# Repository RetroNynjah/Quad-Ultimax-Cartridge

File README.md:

# Retro Ninja Quad Ultimax Cartridge

Eagle schematics and board for a C64 Ultimax cartridge with two-bit ROM selector DIP switch (or jumpers). It's based on a 27256 type EPROM and can fit four 64Kbit (8KB) Ultimax ROM images.

Combine up to four 8KB ROM files into one bigger file before burning EPROM.

The DIP switch is optional. Leave it out if all you need is one 8KB ROM. The DIP switch can also be replaced by a couple of jumpers.

Gerber files and 3D-printable enclosure included.

## BOM
 |Component|Pcs |Name|Comment|
 |:--------|---:|:---|:------|
 | 27256/27C256 EPROM DIP-28| 1 | IC1 | Or compatible EPROM |
 | 2-pos dip switch | 1 | BT1| Optional. CT2062-ND from Digikey or similar | 
 | 100nF ceramic capacitor | 1 | C1 ||
 | 10k resistor | 2 | R1, R2 ||
 
Retro Ninja

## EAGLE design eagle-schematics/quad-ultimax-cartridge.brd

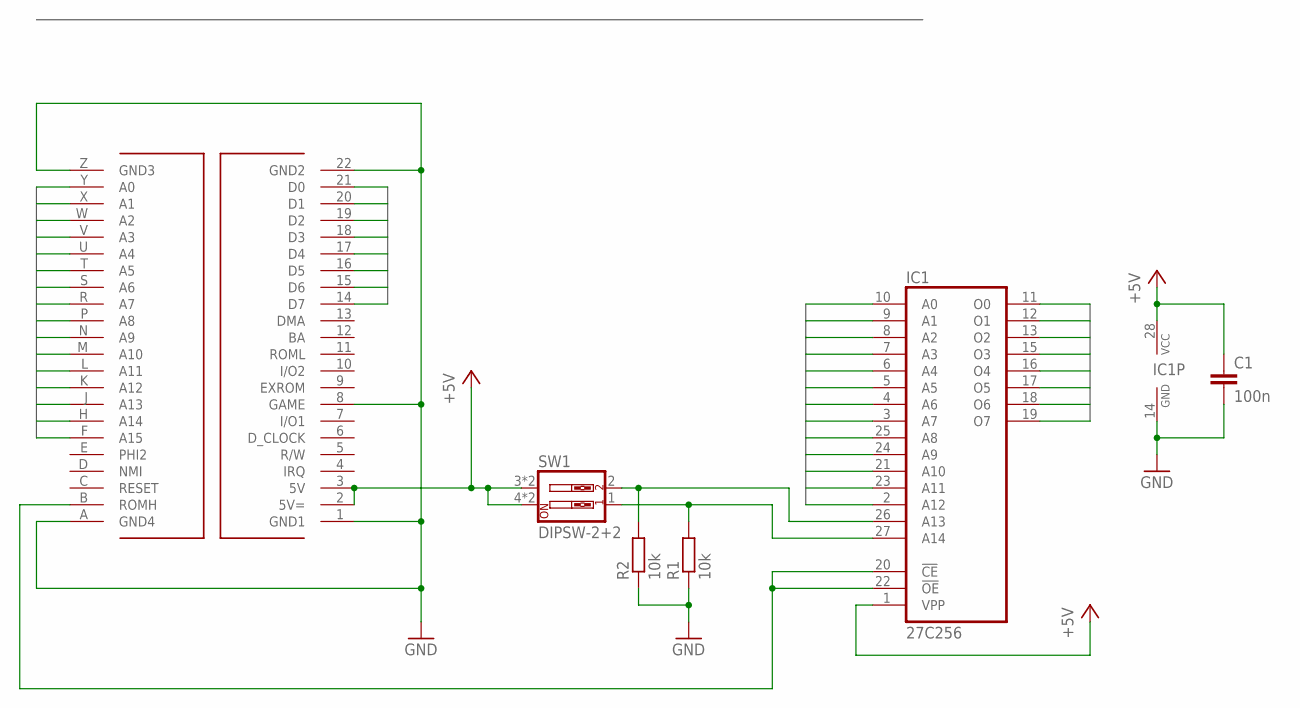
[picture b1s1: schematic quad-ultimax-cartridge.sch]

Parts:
C1: 100n; CAP_5MM_2.5X5.0_ROUND
IC1: 27C256; DIL28
R1, R2: 10k; 0207/10
SW1: DIPSW-2+2; DIPSW2+2
U$1: C64CARTRIDGE_BOARD_CONNECTOR; C64_CARTRIDGE_BOARDEDGE

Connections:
+5V: C1.1, IC1.1 (VPP), IC1.28 (VCC), SW1.3, SW1.4, SW1.5 (3), SW1.6 (4), U$1.2 (5V=), U$1.3 (5V)
A0: IC1.10 (A0), U$1.Y (A0)
A1: IC1.9 (A1), U$1.X (A1)
A2: IC1.8 (A2), U$1.W (A2)
A3: IC1.7 (A3), U$1.V (A3)
A4: IC1.6 (A4), U$1.U (A4)
A5: IC1.5 (A5), U$1.T (A5)
A6: IC1.4 (A6), U$1.S (A6)
A7: IC1.3 (A7), U$1.R (A7)
A8: IC1.25 (A8), U$1.P (A8)
A9: IC1.24 (A9), U$1.N (A9)
A10: IC1.21 (A10), U$1.M (A10)
A11: IC1.23 (A11), U$1.L (A11)
A12: IC1.2 (A12), U$1.K (A12)
A13: U$1.J (A13)
A14: U$1.H (A14)
A15: U$1.F (A15)
D0: IC1.11 (O0), U$1.21 (D0)
D1: IC1.12 (O1), U$1.20 (D1)
D2: IC1.13 (O2), U$1.19 (D2)
D3: IC1.15 (O3), U$1.18 (D3)
D4: IC1.16 (O4), U$1.17 (D4)
D5: IC1.17 (O5), U$1.16 (D5)
D6: IC1.18 (O6), U$1.15 (D6)
D7: IC1.19 (O7), U$1.14 (D7)
GND: C1.2, IC1.14 (GND), R1.1, R2.1, U$1.1 (GND1), U$1.8 (GAME), U$1.22 (GND2), U$1.A (GND4), U$1.Z (GND3)
unnamed: IC1.20 (!CE), IC1.22 (!OE), U$1.B (ROMH)
unnamed: IC1.26 (A13), R2.2, SW1.2
unnamed: IC1.27 (A14), R1.2, SW1.1

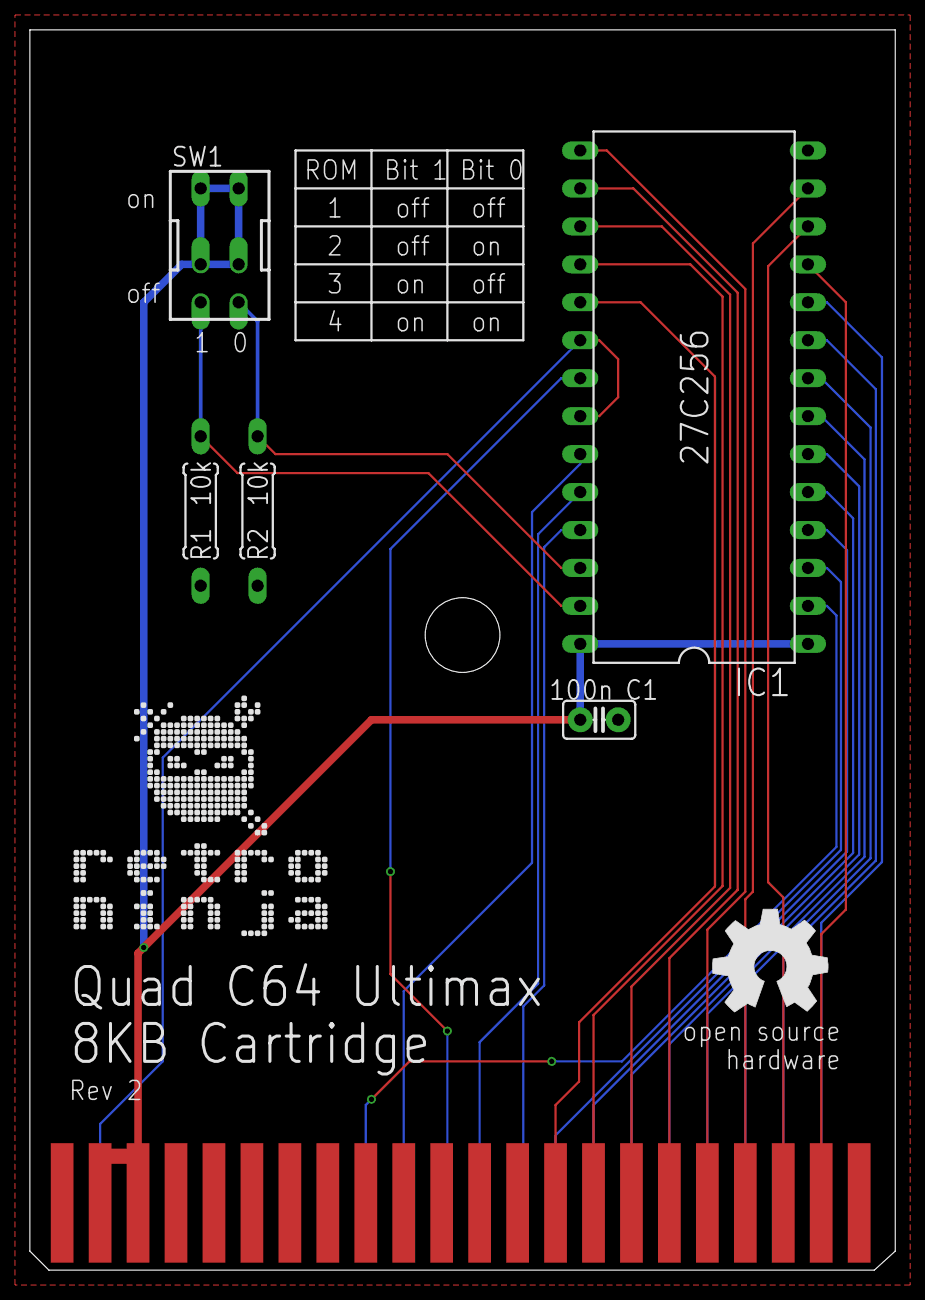
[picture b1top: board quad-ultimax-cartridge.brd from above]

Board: 2 copper layers, 57.9 x 83.0 mm, 8 parts (0 on the bottom side), 26 nets.

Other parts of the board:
U$2: RETRONINJA_TEXT_17MM
U$3: OSHW_8MM

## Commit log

2019-12-19 added schematics, stl files and images
2019-12-19 Updated images and BOM
2019-12-19 Update schematics
